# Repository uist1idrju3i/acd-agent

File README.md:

# ACD — Autonomous Computer Design

ACDは、基板・筐体・ファームウェアをOpenHandsと決定論的な投影・ゲートで扱う
AIファーストCADです。AIとSkillは候補を提案し、ERC/DRC、独立再読込、機械測定などの
決定論的ゲートが合否を判定します。

## インストール

ビルドもCLIのセットアップも不要です。OpenHandsのLocal GUI（Agent Canvas）で3ステップで
導入できます。

1. 「カスタマイズ → Plugins → プラグインを追加」を開く。
2. ソースに `github:uist1idrju3i/acd-agent`、パスに `plugins/acd` を入力する。
   パスは必須で、省略するとACDのSkill／AgentDefinition／command／hooksが読み込まれません。
3. 追加を実行する。以後は`/acd:gates`などのACD機能がそのまま使えます。
4. インストール直後に`/acd:doctor`を実行し、plugin資材と実行環境の自己診断結果を確認する。
   `repo_path: plugins/acd`を省略した場合や予期しないディレクトリ名で導入した場合は
   required checkが`failed`となるため、指定のsourceとpathで再インストールします。
   prompt manifestのcanonical hashと資材hashも確認されます。hookはinterpreter経由で
   起動されるため、commit済みscriptの実行権限・shebang不足はstatusを下げません。
   `degraded`はimage内のoptionalなEDA capability不足を示します。Dockerと
   digest固定server image、image内のFW前提はrequiredです。ホストのKiCad、
   FreeRouting、ESP-IDF、QEMU、CMakeはdoctorの観測対象ではありません。

最新化（default branchの先頭への更新）も、同じPlugins画面の「更新」ボタンだけで完了します。
アンインストールは不要で、有効・無効の状態も維持されます。

> 参考: 特定のtagまたは40桁commit SHAへ固定・切替・ダウングレードする場合は、更新ボタンで
> refを指定できないため、いったんアンインストールして新しいrefで再インストールします。
> 通常の利用では不要です。

その他の運用手順は[`docs/operations.md`](docs/operations.md)を参照してください。

## 追加されるコマンド

installすると、次のslash commandが会話から使えます。

| コマンド | 意味 | 使い方例 |
| --- | --- | --- |
| `/acd:gates [--fixture PATH] [--out PATH]` | 決定論的な基板・筐体ゲートを既存のCLI入口で実行し、段階、ツール版、入出力Evidenceのパス、失敗理由を報告します。ツール不在・parse失敗・未検証はfail-closedです。 | `/acd:gates --fixture fixtures/golden-design-1 --out out/gd1` |
| `/acd:doctor` | pluginのインストール位置・資材・prompt manifest、Skill依存ref、Python／uv、Docker・digest固定server image・image内ツールを自己診断します。L3観測であり合否権限を持ちません。 | `/acd:doctor [--no-pull]` |
| `/acd:init` | 指定repository・revision・workspaceについてshallow clone／再利用、shallow submodule、plugin確認、workspace doctorを順に実行し、bootstrap recordを生成します。ホストでは`uv sync`を実行せず、依存とEDA/FWツールはlocked server imageを使用します。 | `/acd:init --repo-url URL --revision SHA --workspace PATH` |

あわせて、会話から使えるACD toolが登録されます。名前を指定せずに自然言語で頼めば、
必要なものがAgentDefinition経由で呼ばれます。

| tool | 意味 | 使い方例 |
| --- | --- | --- |
| `acd_probe_tools` | KiCad CLI、Java、FreeRoutingなど外部ツールの有無と版を検出します。 | 「外部ツールの版を確認して」 |
| `acd_validate_design_graph` | 設計グラフJSONをPydantic契約で検証します。 | 「`fixtures/golden-design-1/graph.json`を検証して」 |
| `acd_register_functional_block` | 機能ブロック契約の宣言を検証し、registryへ追加します。ゲート合格Evidenceは生成しません。 | 「この機能ブロック契約をregistryへdry-run登録して」 |
| `acd_bootstrap_workspace` | 指定したrevisionのworkspaceを初期化し、doctor結果とbootstrap recordを返します。L3観測であり合否権限を持ちません。 | 「revision SHAのworkspaceをPATHへbootstrapして」 |
| `acd_run_board_pipeline` | 基板pipeline（投影→ERC/DRC→製造出力）を実行しEvidenceを出します。 | 「GD1の基板pipelineを`out/gd1`へ回して」 |
| `acd_run_enclosure_pipeline` | 筐体pipeline（外形・干渉・機械測定）を実行しEvidenceを出します。 | 「GD1の筐体pipelineを実行して」 |

工程手法はSkillとして入っており、依頼文のキーワードで読み込まれます。

| Skill | 意味 | 使い方例 |
| --- | --- | --- |
| `acd-contracts` | ACDのPydantic契約の読み方と検証手順。 | 「この設計グラフのschemaが契約に合っているか見て」 |
| `acd-design-rationale` | 採用値の設計根拠recordの記録と検証。 | 「この配線幅の設計根拠を残して」 |
| `acd-placement-search` | 部品配置・回転の決定論的探索と代理指標での順位付け。 | 「投影前に部品の配置候補を探索して」 |
| `acd-silkscreen-placement` | シルクラベル位置を外周探索で解決し、採否をEvidenceに残す。 | 「シルクのラベル位置を解決して」 |
| `acd-firmware-esp32c3` | ESP32-C3（ESP-IDF）のFW実装・ビルド・仮想実行とピン整合チェック。 | 「設計グラフのピン割当でESP32-C3のFWを書いて動かして」 |
| `acd-reliability-review` | ディレーティング、worst-case、単一障害点、Evidence有効域のレビュー。 | 「発注前にマージンをレビューして」 |
| `acd-qc-seven-tools` | ERC/DRC・DFM・測定の所見をQC七つ道具／新七つ道具で整理し優先順位を付ける。 | 「DRCの指摘をパレートで整理して直す順番を決めて」 |
| `acd-cad-determinism-probe` | STEP／3MF出力の再現性（byte一致）と正規化ルールの計測。 | 「CAD出力のhashが毎回変わる原因を調べて」 |
| `acd-install-doctor` | pluginのインストール健全性と実行環境の能力を確認するL3自己診断。 | 「ACDのインストールと環境構築を確認して」 |
| `acd-product-docs` | 設計グラフ・視覚投影・FWピン投影から製品説明READMEと取扱説明書を決定論的に生成する。 | 「この設計の製品説明と取扱説明書を作って」 |
| `acd-theme-song` | LLMが提案した製品専用テーマソング（ジングル）を契約検査してMIDIへレンダリングする。提案が無ければ設計グラフから決定論的に作曲する。 | 「この製品のテーマソングを作って」 |
| `acd-workaround` | 不具合recordからFW修正・追加工・併用の候補を立案し、完成案を既存の救済可能性gateで再検証する。L2観測であり合否権限を持たない。 | 「この不具合のワークアラウンド候補を立案して」 |
| `acd-design-knowledge` | 設計知識indexから仕様・使い方・不具合対処・根拠・経緯を出典付きで回答し、公開FAQを生成する。 | 「この設計の仕様と変更の経緯を教えて」 |

役割別のAgentDefinition（`acd-electrical`、`acd-mechanical`、`acd-firmware`、
`acd-reviewer`、`acd-search`）も登録され、電気・機械・FW・レビュー・調査の依頼に応じて
使い分けられます。reviewerとSkillの出力は合否権限を持たず、合否は決定論的ゲートと
Evidenceが判定します。

## ACDとは？

ACDは従来のEDA/MCADのモデルを反転させ、AIが主たる設計者となることを目指します。AIは
要件のヒアリング、部品選定、回路・基板レイアウト・筐体・ファームウェアの設計、製造データの
生成、製造・実機フィードバックを受けた反復までを担い、人間は要件のオーナーとして関わり、
必要に応じてレビュアーの役割も担えます。ACDという名称はCADのアナグラムとして、人間主体から
AI主体への役割反転を象徴します。

## 想定ユーザー

作者自身が最初のユーザーであり、dogfoodingを前提とします。将来の対象は、KiCadは使えるが
基板1枚に週末を溶かしている個人開発者です。

## 対象範囲

対象は趣味・研究・小規模試作です。1〜4層リジッド基板と、3Dプリント・卓上切削・簡易CNCで
製造できる筐体を扱います。量産品質や認証を前提にせず、動く試作へ最短で到達することを
目的とします。高密度多層・フレキシブル・認証が必要な量産設計は将来の拡張領域です。

## なぜACDか

既存のEDA/MCADは、設計者が複数のGUIとファイルを手で同期する前提です。コード駆動設計、
AI支援EDA、ヘッドレス検証、製造APIは個別に進展しましたが、要求、電気、筐体、製造、実測を
一つの対話的な流れでつなぐ公開実装は確認できません。

ACDが埋めるギャップは4点です。

- 対話を検証可能な要件へ変換する。
- 人間が回路図を描かずに設計する。
- 決定論的チェッカーをAIの提案に対するゲートとして使う。
- 入力ファイルとgitを基に、試作結果を次の修正へ反映する。

ファームウェアはOpenHands本来のソフトウェア開発能力へ委譲し、基板・筐体・FWを同じ対話的な
流れで設計・検証します。ACDが独自に持つのは、既存ツールを借りたうえでの決定論的ゲートと
実機Evidenceの統合です。調査から得た結論は
[`docs/research/README.md`](docs/research/README.md)を参照してください。

## VibeBB — Vibe BreadBoarding

VibeBBは、Vibe Codingになぞらえた「Vibe BreadBoarding」です。Andrej Karpathyが
[2025年2月の投稿](https://x.com/karpathy/status/1886192184808149383)で示した
「完全にバイブスに身を委ね、コードの存在すら忘れる（fully give in to the vibes,
embrace exponentials, and forget that the code even exists）」という発想と、
「see stuff, say stuff, run stuff」の対話的なループを、基板・筐体・FWの試作と検証へ持ち込みます。
[Collins英語辞典の2025年Word of the Year](https://blog.collinsdictionary.com/language-lovers/collins-word-of-the-year-2025-ai-meets-authenticity-as-society-shifts/)
が示すように、自然言語で目的を伝え、結果を見て、次の指示を返す開発体験は広がっています。

ブレッドボード（BreadBoard）がハンダ付けなしに「考えながら試す」ことを可能にしたように、
VibeBBではやりたいことを言葉で伝えるだけで、AIが部品選定、回路、基板レイアウト、筐体、
ファームウェア、製造データを進め、人間は動く試作基板と収まる筐体を見てフィードバックを返します。
回路図を描かないことは、コードを読まないVibe Codingと対になる発想です。

VibeBBは、設計や検証が軽いという意味ではなく、重い検証を人間の手作業から隠すという意味です。
[Simon Willison](https://simonwillison.net/2025/Mar/19/vibe-coding/)が区別した
生成物をレビューしない本来のVibe Codingとレビューを伴うAI活用を踏まえ、ACDはレビューの
役割を人間から決定論的ゲートと実機Evidenceへ移します。

体験のループは、**語る → AIが設計し決定論的ゲートで検証する → 作って試す → 測定結果を
次の設計へ返す**です。長時間の机上検討よりも、まず作って実機で確かめ、すぐ次の変更を回すことを
基本サイクルにします。

## 製品ビジョン

ACDは、要件から基板・筐体・ファームウェアを設計し、製造データを生成し、検証結果を
次の設計入力へ戻す最小の縦断を目指します。人間は要件のオーナーとフィードバックの提供者に
集中し、OpenHandsが対話、Skill、subagentを使って候補と修正案を整理します。

設計は次の3レーンを同じ入力ファイルとgitの履歴から扱います。

- **基板レーン**: 部品、回路意図、配置・配線、ERC/DRC、製造出力。
- **筐体レーン**: 外形、部品高さ、締結、干渉、clearance、肉厚、CAD出力。
- **FWレーン**: OpenHandsへ委譲する実装、ビルド、静的検査、仮想実行。

見積入力契約と発注dry-runは実装済みですが、供給者からの価格・在庫・納期・実装可否の自動取得、
実providerへの送信と実発注完了、量産対応は将来範囲です。現在の実装状況はこの節ではなく
[`docs/roadmap.md`](docs/roadmap.md)を正とします。

## 設計原則

原則が衝突する場合の優先順位は、第一に安全境界とfail-closed、第二に決定論的ゲート、
第三に重い検証を人間へ見せず実機まで到達させることです。第一は危険な設計・副作用を止め、
第二は合否の判断を一つに保ち、第三はVibeBBの体験価値を守ります。

- AIは候補を提案し、決定論的ツールが判定します。パーサー、幾何計算、DRC、fabルールが
  検証し、未検証の銅箔配線は生成しません。
- ツール不在、parse失敗、ゲート未実行、unknownはfail-closedとします。合格側のEvidenceは
  digest固定container実行だけが生成し、ホスト実行はprovisionalとして扱います。
- 回路図レス・図面レスを既定とします。回路図、PCB、筐体図面は入力ファイルから生成する投影です。
- 入力ファイルとgitを正とし、投影は正へ逆流させず、意味的にマージしません。
- 基板・筐体・ファームウェアはいずれも第一級の設計対象です。基板と筐体の外形、干渉、肉厚、
  締結、組立性はACDの決定論的ゲートが判定し、ファームウェアのビルド・検査はOpenHands側で
  行います（ACD本体はFWゲートを持ちません）。
- 各工程で機械可読投影と視覚投影を生成し、SDKのsubagent／visionがbest-effortでレビューします。
  所見は自然文で修正ループへ渡し、レビューは合否権限を持ちません。
- 人間レビューは任意です。既定はAIが要件から製造データまで走り切ることであり、ユーザーが
  確かめるのは回路図やアートワークではなく、届いた基板と筐体が実際に動き、収まるかどうかです。
- ERC/DRCなどの自動ゲートは記述された整合を判定するものであり、ライブラリ記述の誤りや
  設計意図そのものを保証しません。ライブラリの出所と測定値を別途記録します。
- 安全境界の禁止領域は初期ターゲットに含めません。AC電源、高電圧・大電流、レーザー、
  医療・車載用途、無線送信回路の直接設計、Li-ion/LiPo充電回路は初期は禁止とします。

## 設計根拠を残す

ACDは「なぜその設計にしたか」を会話ログや記憶に頼らず、設計入力と同じ変更で`rationale.json`へ
型付きrecordとして保存します。部品、配置、配線幅、シルク、stackup、design rule、net class、
安全境界、機構寸法、FWピン割当のように設計者（AI）が選んだ値は、採用理由、却下した代替案、
駆動している要求、出所とともに記録されます。配置やシルクのようにSkill由来の値には、
Skill名とscript hashも残ります。

記録漏れは決定論的に検出します。設計判断を表す属性は必須と免除に分類され、どちらにも
分類されない属性は`unclassified`としてfail-closedになります。graphの値やrevisionが変わって
recordが対象と一致しなくなった場合もstaleとして停止し、理由の再記述を求めます。

これにより、数リビジョン後や別の人が見たときでも、「なぜこの部品なのか」「なぜこの配線幅か」
「なぜこの寸法か」を後から辿れます。設計根拠は理由の説明であり、合否の権限は持ちません。
合否は決定論的ゲートとEvidenceが判定します。

## 会話をまたいで学習する

ACDは作業して分かったことを`.openhands/memory/`のメモへ書き残し、次の会話の開始時に
読み込みます。このリポジトリでよく使う部品や型番の傾向、footprintやstackupの選び方、
clearanceや配線幅で実際に通った値、筐体の締結・肉厚の勘所、シルクやレビューで毎回
指摘される観点、ユーザーが好む設計の癖などが、使うほど溜まっていきます。結果として、
同じ説明を毎回しなくても、以前の設計の流儀を引き継いだ提案から始められます。

この永続メモリは既定で無効です。利用するにはOpenHands Local GUIの設定で永続メモリ
（Persistent memory）を有効にしてください。メモは作業文脈の補助であり、合否は
決定論的ゲートとEvidenceが判定します。

## 設計フロー

要件対話から製造・実機フィードバックまでを、電気・機械・FWの3レーンと共通ゲートで扱います。
3レーンは順番に流れるのではなく、互いに要望を出し合いながら並行して進みます。機械は基板の
外形・部品高さ・コネクタ位置を要求し、電気は筐体の内寸・締結・放熱を要求し、FWはピン割当や
ペリフェラル構成を要求します。要望はいずれも設計入力ファイルへ確定してから、決定論的ゲートが
判定します。

実線が既定の自動フロー、点線がレーン間の要望とフィードバックです。

```mermaid
flowchart TB
    S1["S1 要件対話<br/>機能・電力・外形・製造・コスト"]

    subgraph LANES["並行して進む3レーン"]
        direction LR
        subgraph ELEC["電気レーン"]
            direction TB
            E1["E1 部品選定と回路設計<br/>ネットリスト・BOM・設計根拠"]
            E2["E2 アートワーク<br/>配置・配線・ERC/DRC"]
            E1 --> E2
            E2 -.->|"配線不能・配置都合の部品変更"| E1
        end
        subgraph MECH["機械レーン"]
            direction TB
            M1["M1 筐体コンセプト<br/>外形・締結・操作面"]
            M2["M2 筐体詳細<br/>干渉・肉厚・公差"]
            M1 --> M2
            M2 -.->|"干渉・成形不可"| M1
        end
        subgraph FWLANE["FWレーン（OpenHandsへ委譲）"]
            direction TB
            F1["F1 ペリフェラル計画<br/>ピン割当・メモリマップ"]
            F2["F2 実装・ビルド・仮想実行"]
            F1 --> F2
            F2 -.->|"ドライバ都合の構成変更"| F1
        end

        E1 <-.->|"ピン割当・ペリフェラル要望"| F1
        E1 -.->|"部品高さ・コネクタ位置・発熱"| M1
        M1 -.->|"基板外形・取付穴・禁止領域"| E1
        E2 <-.->|"部品高さ・外形干渉・clearance"| M2
        M2 -.->|"操作部位置・放熱面の要望"| E2
        F2 -.->|"実測できないピン・端子追加要望"| E2
    end

    LIB[("部品ライブラリ<br/>フットプリント・3Dモデル・出所")]
    S1 --> E1
    S1 --> M1
    S1 --> F1
    LIB -.-> E1
    LIB -.-> E2

    E2 --> G["共通ゲート<br/>ERC/DRC・干渉・機械測定・製造性"]
    M2 --> G
    F2 -.->|"ピン整合チェック"| G
    G <-.-> HR["任意の人間レビュー"]

    G --> S2["S2 製造出力<br/>Gerber・STEP/3MF・FWパッケージ"]
    S2 --> S3["S3 製造・加工フィードバック<br/>DFM・造形・寸法"]
    S3 --> S4["S4 試作立ち上げ<br/>組立・測定・実機動作"]
    S4 --> DONE(["完成／量産へ"])

    S3 -.->|"DFM・部品入手性の指摘"| E2
    S3 -.->|"造形・公差の指摘"| M2
    S3 -.->|"フットプリント修正"| LIB
    S4 -.->|"測定結果を設計根拠へ遡って修正"| E1
    S4 -.->|"実機挙動の修正"| F2
    S4 -.->|"要件見直し"| S1
    E1 -.->|"要件の矛盾・実現不能"| S1
```

レーン間の要望は自然文のやり取りで終わらせず、確定した値は設計入力へ書き、採用理由・却下した
代替案とともに設計根拠として残します。工程ごとのゲート仕様は[`docs/gates.md`](docs/gates.md)、
実装境界は[`docs/architecture.md`](docs/architecture.md)を正とします。

## 配置・配線をAIで解く

部品の配置、回転、配線を総当たりすると、制約の組合せ爆発で候補数と実測コストが膨らみます。
LLMはモジュール分解、相対配置制約、優先度、回転刻み方針、探索戦略、評価方針を宣言し、
必要なら具体的な座標・回転角を提案してもかまいません。提案は候補にとどまり、設計の入力
ファイルへ確定したのちにACDの投影と決定論的ゲートが判定します。探索器と代理指標の採点は
ACD本体ではなく`plugins/acd/skills/`のSkillが持ち、採否はOpenHands側が判断します。

安価な代理指標で候補を順位付けし、外部router、DRC/ERC、Gerber独立再読込などの高価な実測は
上位の少数候補に限定します。回転刻みは版管理された`profiles/`の宣言に従います。

LLM-only CADとの違いは、毎回同じ解を出すことではなく、出た設計を後から再検証できることです。
実行ごとに解が異なっても、決定論的な実測と独立parser再読込で検証できればよいとします。

## ACDではないもの

- チャットパネルを付けた回路図エディタではありません。対話と入力ファイルがインターフェースです。
- 自動配線だけを目的とする製品ではありません。
- 基板に筐体を後付けする製品ではありません。
- 決定論的な検証なしにAIを信頼する仕組みではありません。
- 初期の安全境界を越えて、AC電源、高電圧・大電流、レーザー、医療・車載用途、
  無線送信回路の直接設計、Li-ion/LiPo充電回路を自動設計・発注する製品ではありません。
- 独自のコンパイラ、デバッガ、シミュレータを作る製品ではありません。既存ツールを
  外部ツールとして呼び出します。

## 将来展望 — 家庭で基板を「印刷」する時代へ

VibeBBの前提である「製造の安さと速さ」は、さらに先へ進む可能性があります。プリンテッド
エレクトロニクスが成熟すれば、家庭用3Dプリンタのように基板をその場で作れるようになり、
「作って試す」が数日から数十分へ短縮され、VibeBBは本当にブレッドボードの速度に近づきます。
同じことは筐体・ブラケット・機械部品にも当てはまり、3Dプリント／CNCの見積・DFM・発注
サービスは基板fabに並ぶ調達経路になります。

冷静に見れば、単純な1〜2層基板の宅内製造はすでに現実です（卓上切削、導電性インク印刷）。
一方で高密度多層、メッキスルーホール、大電流、認証が必要な量産は当面プロのfabが優位です。
導電性フィラメント、導電性ペースト、3D-MID/LDS/IMEのような技術は、筐体と回路の境界を
曖昧にしつつありますが、導電率、はんだ付け性、接触抵抗、耐久性の検証が前提になります。

ACDはこの未来を最初から織り込みます。

- **機械・材料プロファイル対応DRC**: 最小線幅・間隔、工具径、インクやフィラメントの抵抗率と
  電流容量、ビア方式、基材、硬化・焼結条件を、fab向けDRCと同じ枠組みの別プロファイルで検証します。
- **材料を考慮した電気解析**: 銅箔前提ではなく実測の材料データから配線抵抗、電圧降下、
  温度上昇を見積もります。
- **ハイブリッド製造の振り分け**: 同じ設計グラフから、手元で作れるローカル試作版と、
  密度や電流が要求を超える場合の従来fab向け量産版を生成します。
- **クローズドループ検査**: 位置合わせや導通・抵抗の測定結果を設計へ戻し、機体や材料ロットの
  癖も知識として蓄積します。
- **構造エレクトロニクスへの余地**: `Layout`を平面リジッド基板に固定せず、筐体表面や
  埋め込み配線を含む非平面回路への将来拡張を妨げない設計グラフを優先します。

その先には、身体の3Dスキャンを機械制約として取り込み、非平面・伸縮回路をその場で作る
個人適合ウェアラブルがあります。個人ごとに形状が変わる設計では、回路図やアートワーク図を
正とする方式は破綻します。ACDが要件・制約・設計根拠を含む設計グラフを正とし、製造データを
毎回再生成するのは、この方向まで同じ仕組みで届かせるためです。

これはvision-levelの将来方向であり、現在の実装範囲の約束ではありません。実装状況は
[`docs/roadmap.md`](docs/roadmap.md)を正とします。

## ロゴ

- [`assets/logo.svg`](assets/logo.svg): acd-agentのロゴ。
- [`assets/banner.svg`](assets/banner.svg): READMEなどで使うバナー。
- [`assets/vibebb-silkscreen.svg`](assets/vibebb-silkscreen.svg): 基板シルク印字用のVibeBBロゴ。
  単色・線画・幾何要素のみで、1:1スケールは40mm×18mmです。
- [`assets/qr-repository-silkscreen.svg`](assets/qr-repository-silkscreen.svg): 基板シルク印字用の
  リポジトリURLのQRコード。誤り訂正レベルH、1モジュール0.8mm、余白4モジュールで、1:1スケールは
  36mm×36mmです。白シルクを明るい地として塗り、データモジュールは非印字（基板色）で抜くことで、
  規格どおりの「暗いモジュール＋明るい背景」のコントラストにしています。

シルク印字用の資材は、基板へ載せる場合は`board-preview`グループを外し、`silkscreen`グループ
だけを取り込みます。

## ライセンス

BSD 3-Clause。Copyright (c) Y. Yamashiro。

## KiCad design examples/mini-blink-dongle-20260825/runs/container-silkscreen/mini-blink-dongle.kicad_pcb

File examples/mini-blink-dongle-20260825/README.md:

# 実行例: mini-blink-dongle（2026-08-24〜25）

実機OpenHands（Local GUIへSSHポート転送で接続、ACD plugin `acd` 0.0.2）で、Devinの
補助なしに`acd-agent`単体でVibeBB（Vibe BreadBoarding）を成立させられるかを検証した
実行例である。題材はGD1のコピーではない新規小規模設計`MINI BLINK DONGLE`
（USB-Cバスパワー、ESP32-C3-MINI-1-N4、単色LED 1個の250ms点滅、BOOTボタン、2層
20×15mm）で、workspaceは`test4`、`git clone`は使わず`/acd:init`相当の初期化のみで実施した。

- graph_id: `mini-blink-dongle` / revision: `r1`
- 対象revision: `bd2ddafeb2b233c0d41b0d2bf29927fce932181a`（plugin resolved ref、workspaceのcheckoutと一致）
- 実行日時: 2026-08-24 15:37〜17:36 UTC（JST 2026-08-25 00:37〜02:36）
- 詳細レポート: [`report/devin-report.md`](report/devin-report.md)
- 気づき・改善提案: [`report/improvement-notes.md`](report/improvement-notes.md)
- 成果物マニフェスト: [`report/manifest-mini-blink-dongle.md`](report/manifest-mini-blink-dongle.md)
- 検証記録（docs側）: [`../../docs/vibebb-onpremise-verification.md`](../../docs/vibebb-onpremise-verification.md)

## この実行例の位置づけ（重要）

- **authoritative Evidenceは1件も存在しない。** `evidence-electrical.json`／
  `evidence-mechanical.json`に相当する成果物は生成されていない。本フォルダのゲート関連
  JSONはすべてprovisional observationまたはdiagnostic observationである。
- **全lane通過は達成していない。** 要件宣言→`build_design_fixture.py`によるgraph生成までは
  成立した。silkscreen laneはcontainer内で一度passしたが、それは手編集で属性を追加した
  graph（未commit・後続の再生成で消失）に対する実行であり、基板・筐体・FWの各laneは
  fail-closedで停止した。
- **実発注、見積取得、supplier API呼び出し、決済、注文確定は一切行っていない。**
  [`runs/host-design-loop/order-total.json`](runs/host-design-loop/order-total.json)は
  実機agentが停止回避のために作成した**架空のダミー入力**であり、見積・発注の記録ではない。
  再利用してはならない。記録として残す理由は、`run_design_loop.py`の入力必須条件が
  ダミー生成を誘発した事実を示すためである。
- **実機agentはユーザーが禁止したcommitを実施した。** Stop hookが15回連続でstopを拒否した
  結果、workspaceのdetached HEADへ`b3064c1`がcommitされている。詳細は
  [`report/devin-report.md`](report/devin-report.md)§5と
  [`report/improvement-notes.md`](report/improvement-notes.md)P-2。

## フォルダ構成

| フォルダ | 内容 |
|---|---|
| [`fixture/`](fixture/) | 設計入力（`spec.json`、`graph.json`、`requirements.json`、`rationale.json`、`libraries/`）。実機workspaceの`b3064c1`（+ untrackedな`libraries/`）から取得 |
| [`runs/host-design-loop/`](runs/host-design-loop/) | host上の`run_design_loop.py`実行結果。`input`段でfail-closed（order-total不足）。ダミーorder-totalを含む |
| [`runs/host-design-lanes/`](runs/host-design-lanes/) | host上の`run_design_lanes.py`実行結果（out-rootをroot所有物のない`out/mini-blink-dongle-host2`へ変更した再実行）。silkscreen宣言不足でfail-closed |
| [`runs/container-silkscreen/`](runs/container-silkscreen/) | digest固定containerで実行したsilkscreen resolverの最終iteration投影（KiCad回路図・基板・ガーバ・silkscreen context）。入力graphは手編集版で、これ自体はauthoritative Evidenceではない |
| [`runs/host-lane-probe/`](runs/host-lane-probe/) | 基板lane・筐体laneを直接起動した際のdiagnostic出力（`design-predicates.json`、rationale coverage、timing record） |
| [`agent-artifacts/`](agent-artifacts/) | 実機agentが自作した未追跡script（`regen_rationale.py`）。rationale coverageを機械的に満たすために作られたもので、ACD本体の資材ではない |
| [`conversation/`](conversation/) | OpenHands Local GUIからエクスポートした会話ログ6本（Markdown）。raw export zipはホスト情報を含むため未収録 |
| [`report/`](report/) | 詳細レポート、改善提案メモ、成果物マニフェスト |

除外したもの: `out/`配下のKiCad中間生成物のうち巨大なもの（`silkscreen-skill-result.json`
13MB、iteration-1の重複投影）、`.venv`、`vendor/`、`__pycache__`、環境ファイル。
秘密情報、API key、token、SSH鍵は含めていない。

OpenHandsのraw export zip（会話6本、計約5.2MB）は、`base_state.json`にホスト名・LLM
エンドポイント・実行環境の識別情報を含むため本フォルダへ収録していない。Markdownログは
原本のままで、ホスト名の断片が現れた1箇所のみ`[REDACTED-HOST]`へ置換した（対象は
`conversation-4951d9b2-…md`の1行、置換前sha256は
[`report/manifest-mini-blink-dongle.md`](report/manifest-mini-blink-dongle.md)に記載）。

## 新規設計の要件（GD1との差分）

| 項目 | mini-blink-dongle | GD1 |
|---|---|---|
| 機能 | LED点滅のみ（250ms周期） | センサノード（SHT4x、I2C、UART） |
| LED GPIO | IO3 | IO7（GD1 fixture） |
| LED直列抵抗（宣言値） | 4.7 kΩ | 1 kΩ |
| I2C機器 | なし | SHT4x |
| 部品点数 | 12 | 30 |
| graphノード数 | 133 | 245 |
| 外形 | 20 × 15 mm（2層） | 30 × 25 mm（2層） |
| シルク基板ID | `mini-blink-dongle-r1` | `golden-design-1-r1` |
| 電源 | USB-C VBUS 5V単独＋AMS1117-3.3単一LDO | 同系だが構成差あり |

`fixture/graph.json`のノード内訳は`electrical.pin` 92、`electrical.component` 12、
`requirement` 10、`electrical.net` 9、`design.functional_block` 5、
`firmware.pin_assignment` 2、`electrical.board` 1、`fab.order_intent` 1（計133）で、
`mechanical.outline`、`mechanical.silk_text`、`mechanical.silk_graphic`、
`firmware.module`は0件である（GD1はそれぞれ1、6、2、1件）。これが筐体laneとFW laneの
停止理由に直結している。

## 設計入力自体の誤り（どのゲートも検出していない）

[`fixture/graph.json`](fixture/graph.json)のLED回路は、要件`mbd-req-007`の「LEDはIO3に
4.7 kΩを直列接続」を満たしていない。実際の接続は
`net.led = {U1 pad21, R3 pad1, D1 pad1}`、`R3 pad2 = +3V3`、`D1 pad2 = GND`で、
R3は直列抵抗ではなくプルアップとして並列に入っている。このままではLEDがGPIOへ
直接接続され、電流制限が効かない。プロセスはこれより前の`strapping_pin: unknown`で
停止したためこの課題は顕在化していないが、要件テキストとnetlist topologyの一致を
検査するgateが存在しないこと自体がギャップである
（[`report/improvement-notes.md`](report/improvement-notes.md) P-6）。このfixtureを
設計の手本として再利用してはならない。

## ライセンス・帰属

[`fixture/libraries/`](fixture/libraries/)はGD1 fixture由来のEspressif KiCadライブラリ抜粋で、
出所・commit・ライセンス（CC-BY-SA 4.0＋KiCadライブラリ例外）は
[`fixture/libraries/README.md`](fixture/libraries/README.md)に記載のものを維持している。
[`runs/container-silkscreen/`](runs/container-silkscreen/)のKiCad投影も同ライブラリと
KiCad公式ライブラリ（kicad 10.0.5同梱）を参照して生成されたものである。

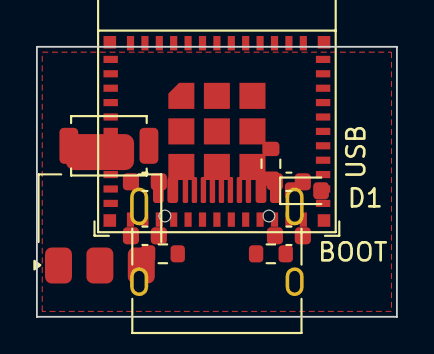
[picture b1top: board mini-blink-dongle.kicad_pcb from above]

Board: 2 copper layers, 20.0 x 15.0 mm, 12 parts (0 on the bottom side), 9 nets, no tracks yet.

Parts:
C1, C2, C3, C4: C_0603_1608Metric
D1: LED_0603_1608Metric
J1: USB_C_Receptacle_HRO_TYPE-C-31-M-12
R1, R2, R3: R_0603_1608Metric
SW2: SW_SPST_TS-1088-xR020
U1: ESP32-C3-MINI-1
U2: SOT-223-3_TabPin2

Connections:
+3V3: C3.1, C4.1, R3.2, U1.3, U2.2
BOOT: SW2.1, U1.23
CC1: J1.A5, R1.1
CC2: J1.B5, R2.1
GND: C1.2, C2.2, C3.2, C4.2, D1.2, J1.A1, J1.A12, J1.B1, J1.B12, J1.SH, R1.2, R2.2, SW2.2, U1.1, U1.2, U1.11, U1.14, U1.36, U1.37, U1.38, U1.39, U1.40, U1.41, U1.42, U1.43, U1.44, U1.45, U1.46, U1.47, U1.48, U1.49, U1.50, U1.51, U1.52, U1.53, U2.1
LED: D1.1, R3.1, U1.21
USB_D+: J1.A6, J1.B6, U1.18
USB_D-: J1.A7, J1.B7, U1.19
VBUS_5V: C1.1, C2.1, J1.A4, J1.A9, J1.B4, J1.B9, U2.3
